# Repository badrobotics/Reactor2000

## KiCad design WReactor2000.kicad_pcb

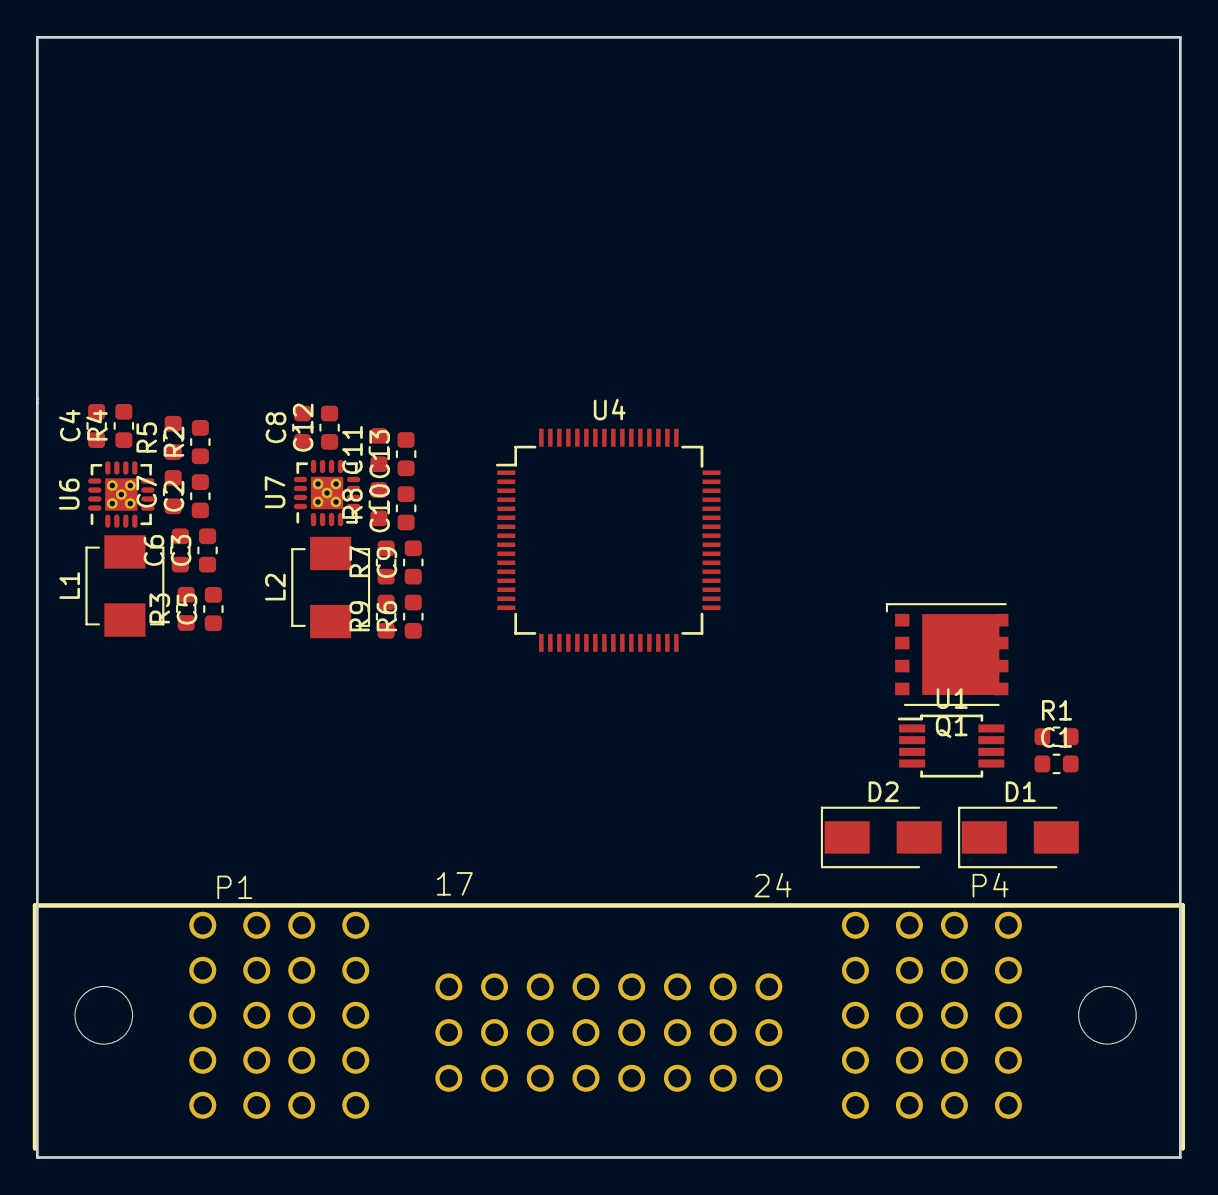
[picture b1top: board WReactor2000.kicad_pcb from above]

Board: 4 copper layers, 63.5 x 62.2 mm, 32 parts (0 on the bottom side), 25 nets, no tracks yet.

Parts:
C1, C7, C13: 47u; C_0603_1608Metric
C2, C8: 2200p; C_0603_1608Metric
C3, C9: 2.2u; C_0603_1608Metric
C4, C10: 330p; C_0603_1608Metric
C5, C11: 22u; C_0603_1608Metric
C6, C12: 0.1u; C_0603_1608Metric
D1: SMAT70A; D_SMA
D2: SMAJ24A; D_SMA
L1, L2: 0.47u; L_Vishay_IHLP-1616
Q1: BSC026N08NS; TDSON-8-1
R1: 1k; R_0603_1608Metric
R2, R6: 20k; R_0603_1608Metric
R3, R7: 210k; R_0603_1608Metric
R4, R8: 115k; R_0603_1608Metric
R5, R9: 25.5; R_0603_1608Metric
U1: LTC4359-MS8; MSOP-8_3x3mm_P0.65mm
U2: ET60T-02-24-02-X-RTX-GP; ET60T-02-24-02-X-RTX-GP-HS
U4: TM4C1230H6PM; LQFP-64_10x10mm_P0.5mm
U6, U7: LTC3604_UD; QFN-16-1EP_3x3mm_P0.5mm_EP2.7x2.7mm_ThermalVias

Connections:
+3V3: C13.1, L2.2, R8.1, U7.8
+5V: C7.1, L1.2, R4.1, U6.8
+12V: C5.1, C11.1, U6.14, U6.15, U6.16, U7.14, U7.15, U7.16
+BATT: D1.1, Q1.1, Q1.2, Q1.3, U1.2, U1.4
/3.3V supply/BST: C12.1, U7.6
/3.3V supply/FB: R8.2, R9.1, U7.11
/3.3V supply/INTVcc: C9.1, U7.7
/3.3V supply/ITH: R6.1, U7.12
/3.3V supply/RT: R7.1, U7.10
/3.3V supply/SW: C12.2, L2.1, U7.3, U7.4
/3.3V supply/TRACK-SS: C8.1, U7.13
/5V supply/BST: C6.1, U6.6
/5V supply/FB: R4.2, R5.1, U6.11
/5V supply/INTVcc: C3.1, U6.7
/5V supply/ITH: R2.1, U6.12
/5V supply/RT: R3.1, U6.10
/5V supply/SW: C6.2, L1.1, U6.3, U6.4
GND: C2.2, C3.2, C4.2, C5.2, C7.2, C8.2, C9.2, C10.2, C11.2, C13.2, R1.2, R3.2, R5.2, R7.2, R9.2, U6.9, U6.17, U7.9, U7.17
unnamed: C1.1, Q1.5, U1.8
unnamed: C1.2, D2.1, R1.1, U1.6
unnamed: C2.1, U6.13
unnamed: C4.1, R2.2
unnamed: C10.1, R6.2
unnamed: D1.2, D2.2
unnamed: Q1.4, U1.1

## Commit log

2019-03-10 dumb-updates
2019-06-29 Create LICENSE
